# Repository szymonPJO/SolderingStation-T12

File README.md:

# Soldering station T12

<table>
    <td></td>
    <td></td>
</table>

## Specification:

- **Ramp-up Time**: 5 seconds to achieve 200°C
- **Measurement Accuracy**: up to ±5%
- **Power**: 75W
- **Instability (Consistency) of Set Temperature**: ±0.2°C
- **Temperature Range**: 0 – 500°C (from room temperature)
- **Number of ADC Samples**: 250
- **Measurement Time** / **Percentage of Measurement Duration (Heating Off)**: 1.4ms / 1.4% (or 0.9ms / 0.9% for temperatures >150°C)
- **PWM Frequency** / **Measurement Frequency**: 50Hz / 10Hz
- **Other**: (futures below)

<!-- # About my motivation

elektroda.
*Translated site from polish! -->

### Features:

- T12 Tips Compatibile
- IPS Display
  - Current and Set Temperature in `°C`
  - Power Output Bar Indicator
  - Settings (PID and GUI)
- Rotary Encoder
- Touch Button (stop/start heating)
- Heating LED
- Switch 230VAC
- Front Panel - PCB made
- Connector GX16 (easy tips replacement)

#### Software Features:

- Efficient Temperature Setting - PID Controller
- Memory - Eeprom
- Autosleep (todo)

## Schematics

<table>
    <tr></tr>
    <tr>
        <td></td>
    </tr>
</table>

## Software requirments

[stlink](https://github.com/stlink-org/stlink?tab=readme-ov-file), kicad (optional)

## Flashing

It's required debuger for flash STM32. STLINK-V2 clone is fine.

```bash
st-flash --reset write soldering-*.bin 0x08000000
```

If you have error then it's probably stm32 clone. It's ok. Blue-Pill boards have clons often. Check `st-info --chipid`. For clones "chipid" is 0 instead 0x0410 or similar. Try to flash with my config file.

```bash
st-flash -c doc/BP_clone.cfg --reset write soldering-*.bin 0x08000000
```

## Assembly Guide

1. First take a look at overall BOM below. Next check [PCB BOM online][preview-bom-v1] or as file in `PCB/{version}/bom/ibom.html`. (I suggest to dowload the repo this point)

   | Part                  | Description                                             | Photo                                                                    |
   | --------------------- | ------------------------------------------------------- | ------------------------------------------------------------------------ |
   | PCB components        | All important components from [PCB BOM][preview-bom-v1] |                                                                          |
   | Housing               | Gainta G762                                             |                                                                          |
   | Power Supply 24V      | 24V/3A or more current (e.g. 24V/4A)                    |     |
   | Power Supply 5V       | 5V/100mA or more current                                |                                                                          |
   | MCU                   | Blue Pill board                                         |                                                                          |
   | Display               | ST7735 SPI 160x80 0.96" module                          |     |
   | Encoder               | Rotary Encoder module                                   |  |
   | Soldering Iron Socket | GX16-5 Socket                                           |                                                                          |
   | Front Panel           | PCB front panel (project in repo folder)                |                                                                          |
   | Knob                  | Knob for encoder                                        |                                                                          |
   | AC Switch             | SPDT                                                    |                                                                          |
   | Other components      | LED or duoLED 3mm, 2x 1nF THT                           |                                                                          |

   Make sure u have all what you need to DIY. Good to check all parts works berore u start assembly

2. If u making PCB by own, remember to:
   <!-- - U can use _Ready-to-print.pdf_ for e.g. iron-on method -->

   - Protect copper by e.g. Rosin
   - Solder wires from "F.cu" layer (may be before drilling, except two connections)

   If u order PCB, remember u can also order PCB-front-board together

3. Soldering SMD (**after drilling**) - BOM [online][preview-bom-v1] or `PCB/*/bom/` can help
4. Soldering THT
5. Mount 24V power supply to device housing and **make separation** between PCB (Plan this housing from mountings things inside)

6. Make power wires from overall schematic for: _Switch, Power suplies, AC connector_ (**Isolate 230V wires and connections**)
7. Make wires and solder from overall schematic (for: _Display, Encoder, etc_) and add 2x 1nF to Encoder module if there is no capacitors
8. **Isolate** and Mount (glue) 5V power supply
9. Connect all together, burn binary and **check that's working**
10. Glue OLED while device works (it would be easier to nice match) to (if u have) PCB-front-board.
11. Let's put everything together now

### Additional assembly tips

- **Be careful** with **AC Power**

- required tools:

  - some working soldering iron (it's funny, but not ironically)
  - some glue (e.g. hotglue or b7000)
  - drilling machine, drills: ~3mm, 0,7mm, 0,9mm (look at kicad brd)
  - tweezer
  - (optional) crimping tool for Dupont Connectors

- good to use:

  - 2.54mm angle pin header + Dupont female Connectors

- Front Panel

  U have to order PCB or drill by CNC. Alternativly try to print 'cut edges' on paper and cut housing plastic plate by knife / drill. The G762 housing have bit soft plastic (maybe ABS) - front/back plates.

## Gallery

Check the `Pictures/` folder! :)

---

#### Imagined Concept:

What I decide to leave at concept phase:

- 907 tips compatibility
- tips recognizing
- measurement of thermocouple cold junction thermistor
- optional li-ion power

### Contributing

Feel free to open Pull Request or some Issue

---

[preview-bom-v1]: https://html-preview.github.io/?url=https://github.com/szymonPJO/SolderingStation-T12/blob/main/PCB/soldering-mainboard-v1.0/bom/ibom.html

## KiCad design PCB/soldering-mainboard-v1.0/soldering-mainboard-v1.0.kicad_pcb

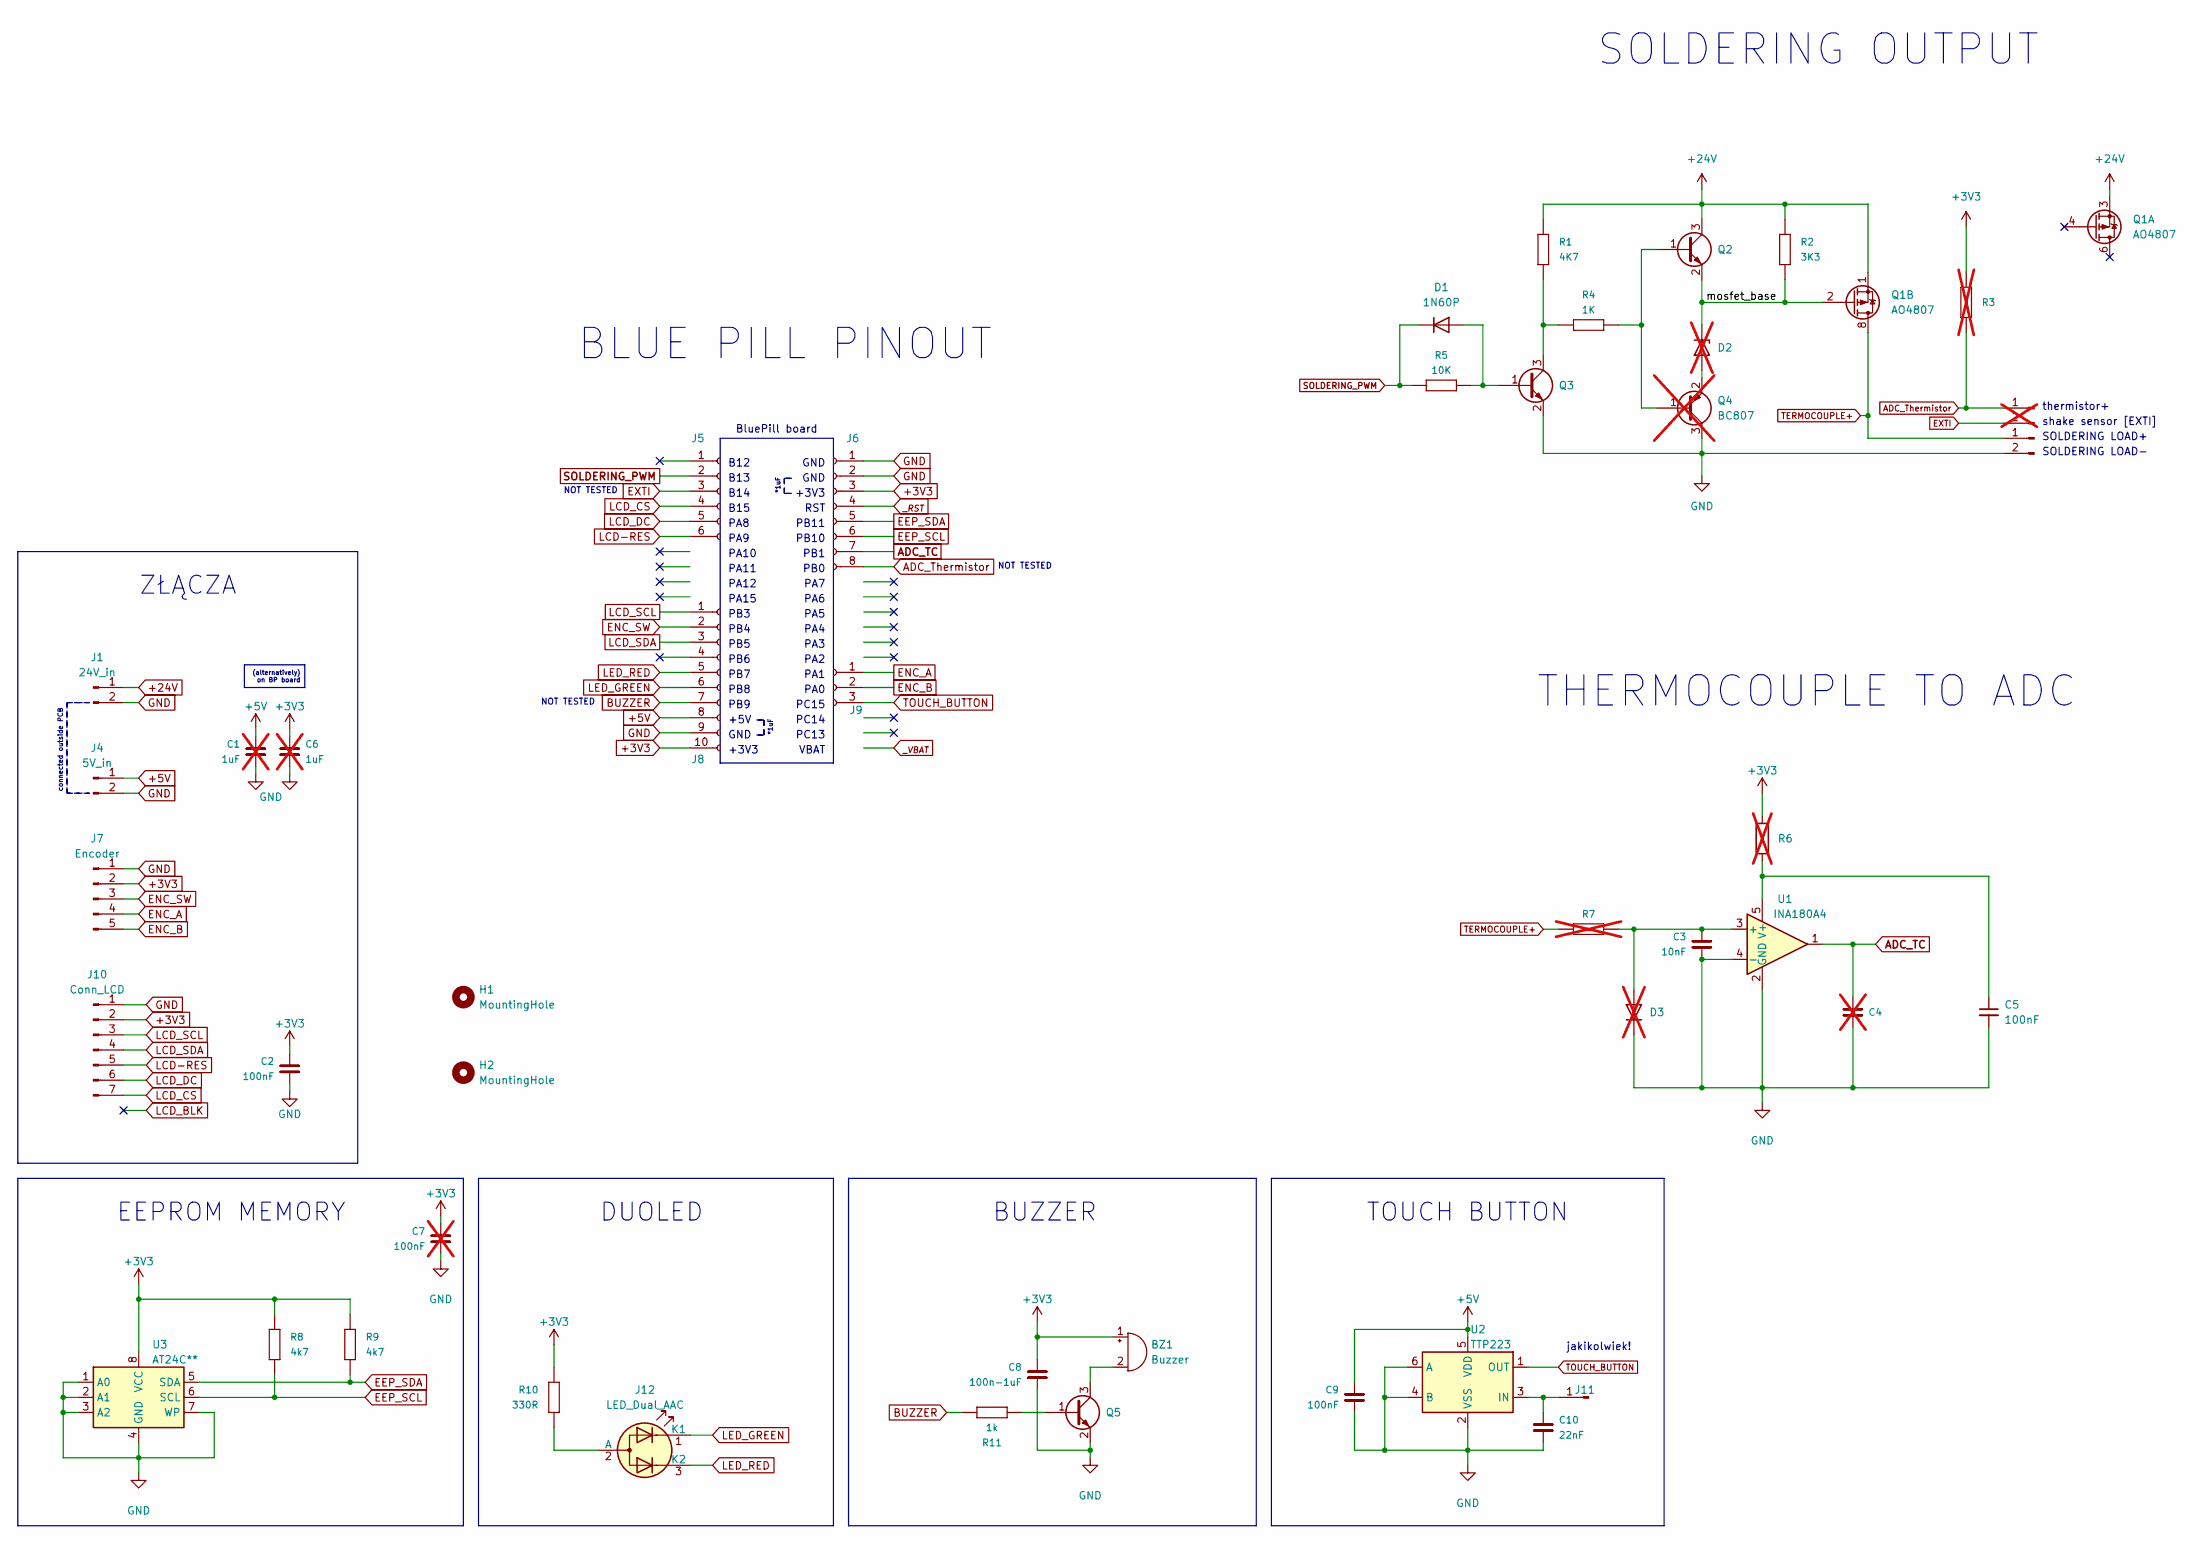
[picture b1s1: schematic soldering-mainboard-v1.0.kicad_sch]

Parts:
BZ1: Buzzer; Buzzer_12x9.5RM7.6
C1, C6: 1uF; C_0805_2012Metric; not fitted
C2, C5, C9: 100nF; C_0805_2012Metric
C3: 10nF; C_0805_2012Metric
C4: C_0805_2012Metric; not fitted
C7: 100nF; C_0805_2012Metric; not fitted
C8: 100n-1uF; C_0805_2012Metric
C10: 22nF; C_0805_2012Metric
D1: 1N60P; D_DO-34_SOD68_P5.08mm_Vertical_AnodeUp
D2, D3: D_Axial_P1.90mm_Vertical; not fitted
H1, H2: MountingHole; MountingHole_2.7mm_M2.5_ISO14580
J1: 24V_in; PinHeader_1x02_P2.54mm_Vertical
J2: PinHeader_1x02_P2.54mm_Vertical; not fitted
J3: Soldering Iron; PinHeader_1x02_P2.54mm_Vertical
J4: 5V_in; PinHeader_1x02_P2.54mm_Vertical
J5: Conn_01x06_Socket; PinSocket_1x06_P2.54mm_Vertical
J6: Conn_01x08_Socket; PinSocket_1x08_P2.54mm_Vertical
J7: Encoder; PinHeader_1x05_P2.54mm_Vertical
J8: Conn_01x10_Socket; PinSocket_1x10_P2.54mm_Vertical
J9: Conn_01x03_Socket; PinSocket_1x03_P2.54mm_Vertical
J10: Conn_LCD; PinHeader_1x07_P2.54mm_Vertical
J11: Conn_01x01_Male; PinHeader_1x01_P2.54mm_Vertical
J12: LED_Dual_AAC; PinHeader_1x03_P2.54mm_Vertical
Q1: AO4807; SOIC-8_3.9x4.9mm_P1.27mm
Q2, Q3, Q5: MMBT3904; TSOT-23
Q4: BC807; TSOT-23; not fitted
R1: 4K7; R_0805_2012Metric
R2: 3K3; R_0805_2012Metric
R3: R_0805_2012Metric; not fitted
R4: 1K; R_0805_2012Metric
R5: 10K; R_0805_2012Metric
R6, R7: SolderJumper-2_P1.9mm_Closed; not fitted
R8, R9: 4k7; R_0805_2012Metric
R10: 330R; R_0805_2012Metric
R11: 1k; R_0805_2012Metric
U1: INA180A4; SOT-23-5
U2: TTP223; SOT-23-6
U3: AT24C**; SOIC-8_3.9x4.9mm_P1.27mm

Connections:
+3V3: BZ1.1 (-), C2.1, C7.1, C8.1, J6.3, J7.2, J8.10, J10.2, R3.2, R6.2, R8.2, R9.2, R10.2, U3.8 (VCC)
+5V: C1.1, C9.1, J4.1, J8.8, U2.5 (VDD)
+24V: J1.1, Q1.1 (S2), Q1.3 (S1), Q2.3 (C), R1.2, R2.2
/mosfet_base: D2.1 (K), Q1.2 (G2), Q2.2 (E), R2.1
ADC_TC: C4.1, J6.7, U1.1
ADC_Thermistor: J2.1, J6.8, R3.1
BUZZER: J8.7, R11.2
EEP_SCL: J6.6, R8.1, U3.6 (SCL)
EEP_SDA: J6.5, R9.1, U3.5 (SDA)
ENC_A: J7.4, J9.1
ENC_B: J7.5, J9.2
ENC_SW: J7.3, J8.2
EXTI: J2.2, J5.3
GND: C1.2, C2.2, C3.2, C4.2, C5.2, C7.2, C8.2, C9.2, C10.2, D3.1 (K), J1.2, J3.2, J4.2, J6.1, J6.2, J7.1, J8.9, J10.1, Q3.2 (E), Q4.3 (C), Q5.2 (E), U1.2 (GND), U1.4 (-), U2.2 (VSS), U2.4 (B), U2.6 (A), U3.1 (A0), U3.2 (A1), U3.3 (A2), U3.4 (GND), U3.7 (WP)
LCD-RES: J5.6, J10.5
LCD_CS: J5.4, J10.7
LCD_DC: J5.5, J10.6
LCD_SCL: J8.1, J10.3
LCD_SDA: J8.3, J10.4
LED_GREEN: J8.6, J12.1 (K1)
LED_RED: J8.5, J12.3 (K2)
unnamed: BZ1.2 (+), Q5.3 (C)
unnamed: D1.2 (A), Q3.1 (B), R5.2
unnamed: D2.2 (A), Q4.2 (E)
unnamed: C3.1, D3.2 (A), R7.2, U1.3 (+)
unnamed: C10.1, J11.1, U2.3 (IN)
unnamed: J12.2 (A), R10.1
unnamed: Q2.1 (B), Q4.1 (B), R4.2
unnamed: Q3.3 (C), R1.1, R4.1
unnamed: Q5.1 (B), R11.1
unnamed: C5.1, R6.1, U1.5 (V+)
SOLDERING_PWM: D1.1 (K), J5.2, R5.1
TERMOCOUPLE+: J3.1, Q1.7 (D2), Q1.8 (D2), R7.1
TOUCH_BUTTON: J9.3, U2.1 (OUT)
_{_RST}: J6.4

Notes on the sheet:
(alternatively) on BP board
PA9
DUOLED
PA2
TOUCH BUTTON
PA7
+5V
ZŁĄCZA
SOLDERING LOAD-
PA15
PC14
jakikolwiek!
PA5
PB5
PA0
NOT TESTED
PB10
VBAT
PB3
B15
PB9
BLUE PILL PINOUT
GND
THERMOCOUPLE TO ADC
*1uF
B13
B14
PA3
B12
PA12
PA10
+3V3
PB7
PA8
PA1
shake sensor [EXTI]
PB8
PB4
PB6
PA11

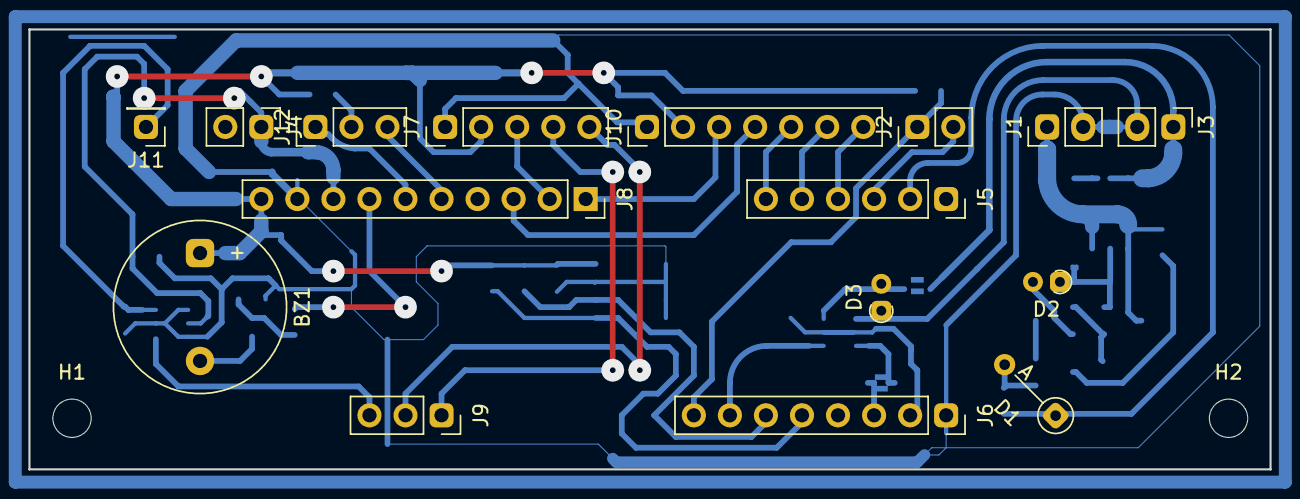
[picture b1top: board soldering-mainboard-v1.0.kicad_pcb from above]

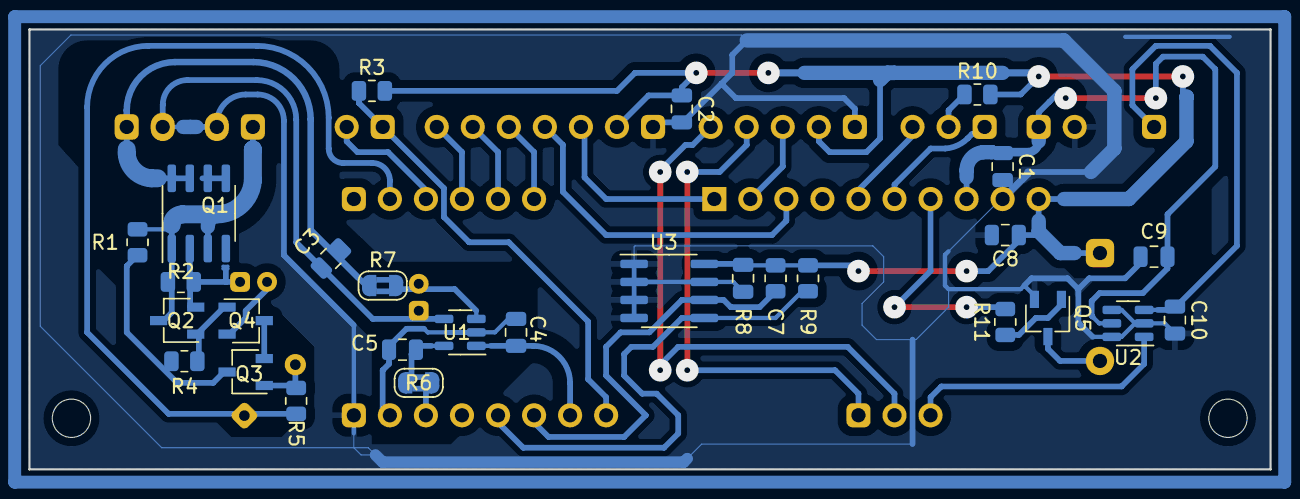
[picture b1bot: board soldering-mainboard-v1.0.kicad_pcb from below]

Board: 4 copper layers, 87.5 x 31.0 mm, 46 parts (28 on the bottom side), 34 nets.

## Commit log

2021-11-05 init-photo^^
2022-01-24 errata i2c img
2023-02-06 rewrite description
2023-02-06 doc: refactor
2023-02-06 doc: small fix
2023-08-04 Update README.md (from gh :O)
2024-03-02 update ;)
    In other words, this is first commit after long break. More like initial commit
2024-03-02 rename
2024-03-02 refactor: fix picture formatting
2024-03-02 doc: link to html-preview from PCB v1
2024-03-02 mesurements and simulations
2024-03-03 Pictures 02.24
2024-03-03 doc images
2024-03-03 refactor doc
2024-03-05 doc: fix misspells
2024-03-05 doc: polski
2024-03-05 exampe pic in table
2024-03-05 doc: pics device inside
2024-03-11 feat: new settings
    fix buzzeer, feat memory for settings, autosleep
    and more

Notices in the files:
README.md:
CC BY-NC 4.0
